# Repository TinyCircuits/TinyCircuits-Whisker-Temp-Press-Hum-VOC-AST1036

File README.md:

# TinyCircuits Wireling Temp Press Hum VOC
# AST1036 Rev1

The design files are located under design_files/ for the TinyCircuits AST1036 Rev 1 PCB. This is a Wireling board which features the BME680 Sensor that is a 4-in-1 sensor including the ability to measure temperature, barometric pressure, humidity, and gas.

Format is in Cadsoft Eagle format - Eagle version 6.2 was used for the original design.

For more infomation on this, check out the product page at TinyCircuits.com

# License:

Design by TinyCircuits.
All design files are released under the Creative Commons Attribution Share-Alike 3.0 License, see the following link for details: http://creativecommons.org/licenses/by-sa/3.0

All text above must be included in any redistribution or derived design

This project uses designs and concepts developed as part of the Arduino project and the LilyPad project.  The TinyCircuits design files themselves (schematics, PCB and libraries) are not directly derived from these works' design files and have been created new, however the concepts and basic architecture behind the TinyDuino and TinyLily products are derived and we thank the hard work of the organizations below for their contributions to open-source hardware:
  
Original Arduino Uno Design by Team Arduino

LilyPad Arduino Design by Leah Buechley and Sparkfun Electronics

Please support the open-source hardware community

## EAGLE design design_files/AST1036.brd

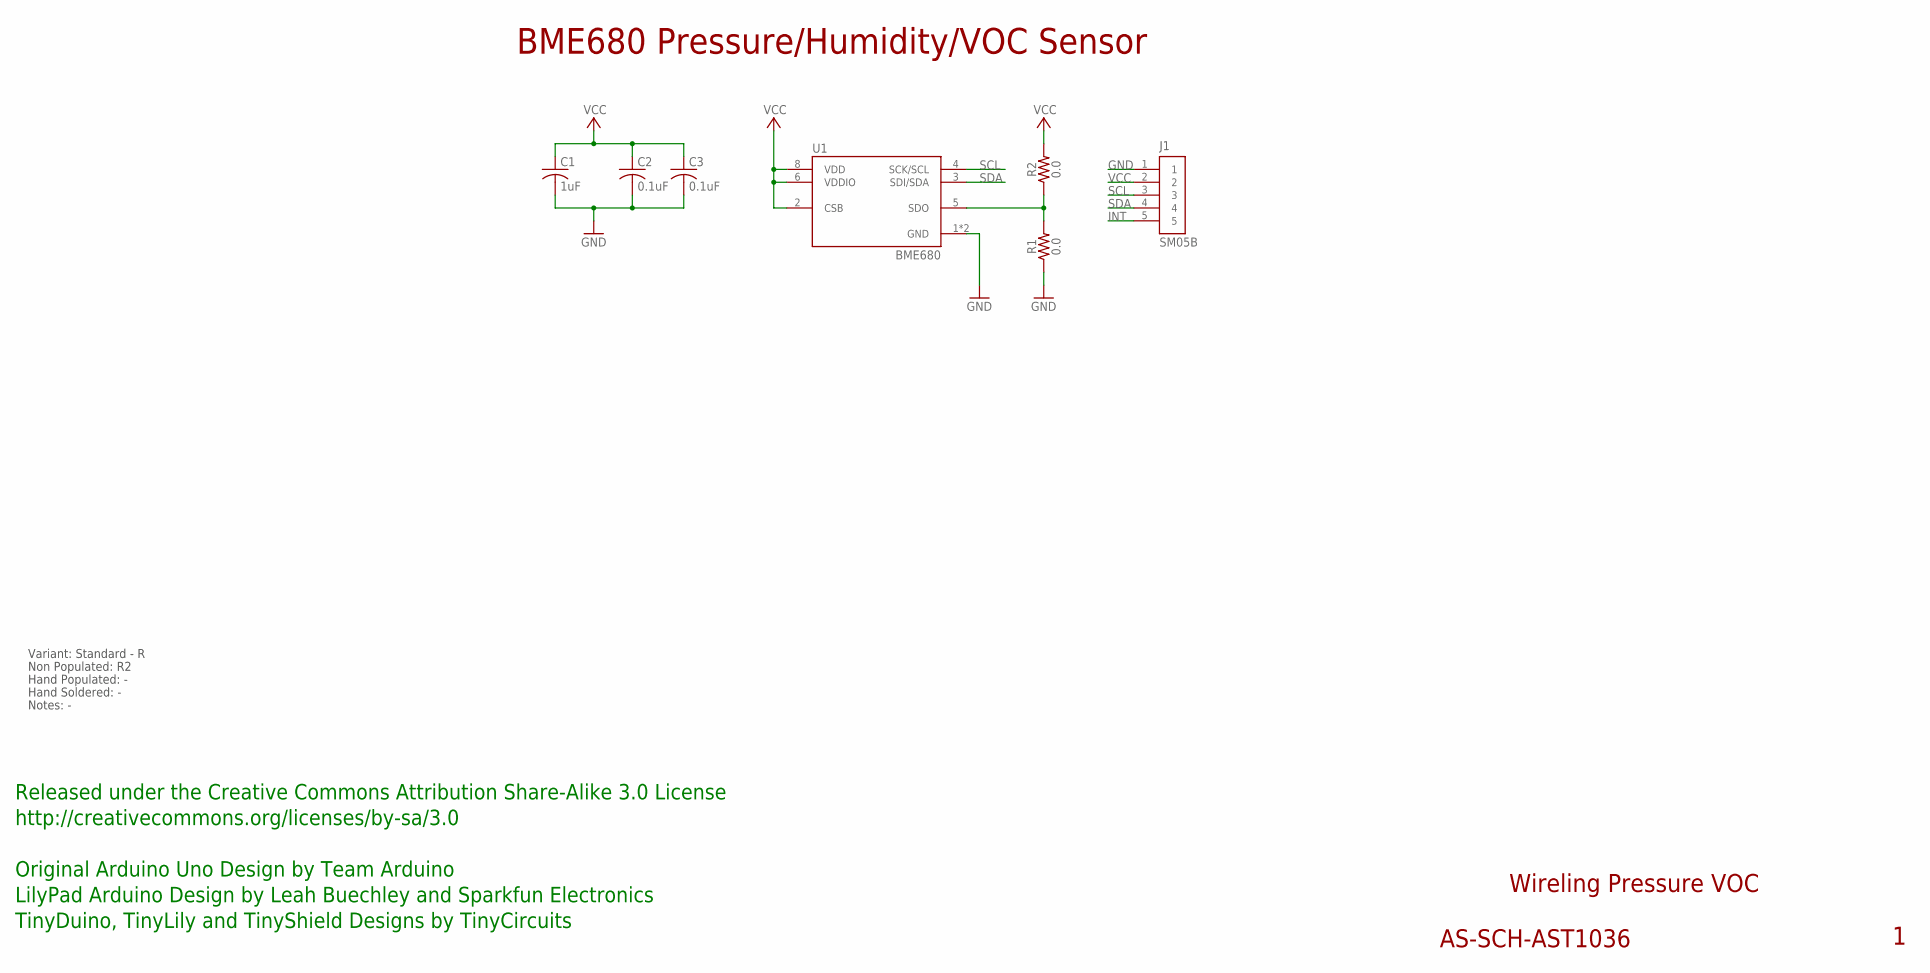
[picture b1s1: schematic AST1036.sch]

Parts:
C1: 1uF; C0603; PARTNO AS-ITM-00410
C2: 0.1uF; C0402
C3: 0.1uF; C0402; PARTNO AS-ITM-00008
J1: SM05B; JST_SH_5X1_EDGE
R1: 0.0; 0402
R2: 0.0; 0402; PARTNO AS-ITM-00076
U1: BME680

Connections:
GND: C1.2, C2.2, C3.2, J1.1, R1.1, U1.1 (GND), U1.7 (GND)
INT: J1.5
unnamed: R1.2, R2.1, U1.5 (SDO)
SCL: J1.3, U1.4 (SCK/SCL)
SDA: J1.4, U1.3 (SDI/SDA)
VCC: C1.1, C2.1, C3.1, J1.2, R2.2, U1.2 (CSB), U1.6 (VDDIO), U1.8 (VDD)

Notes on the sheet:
Wireling Pressure VOC
AS-SCH-AST1036
BME680 Pressure/Humidity/VOC Sensor
Released under the Creative Commons Attribution Share-Alike 3.0 License
http://creativecommons.org/licenses/by-sa/3.0
Original Arduino Uno Design by Team Arduino
TinyDuino, TinyLily and TinyShield Designs by TinyCircuits
LilyPad Arduino Design by Leah Buechley and Sparkfun Electronics
Non Populated: R2
Hand Populated: -
Hand Soldered: -
Notes: -
Variant: Standard - R

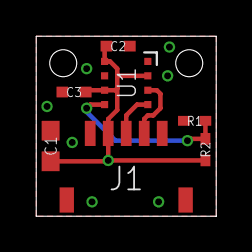
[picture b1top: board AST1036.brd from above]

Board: 2 copper layers, 10.0 x 10.0 mm, 8 parts (0 on the bottom side), 5 nets.

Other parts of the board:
U$1: DOCFIELD-TINYCIRCUITS-PCB

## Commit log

2019-08-01 added example sketch
2019-08-05 added datasheet
2019-12-17 updated documentation
2020-01-14 images & code
2020-01-14 show data
2020-01-15 remove old schematic
2020-02-04 mass image update
2020-08-14 Add CAD data
